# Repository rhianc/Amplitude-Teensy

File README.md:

# PROPRIETARY AMPLITUDE LIGHTING SOFTWARE/HARDWARE REPOSITORY

##  HOW TO CLONE THIS REPO

in unix terminal:

$ git clone --recurse-submodules git@github.com:vfink/amplitude_lights.git

If you do not include the "--recurse-submodules" you will not have the correct library to run the lights

You may need to associate your git account with your computer and should add an SSH key to both your laptop and github account so you don't have to type your password every time. 

## WHERE IS EVERYTHING

24 strip reactive lights:

	master teensy -> amplitude/multi_strip_lights/AmplitudeLights/fftBigBoyMaster
	slave teensy (what you should touch) -> amplitude/multi_strip_lights/AmplitudeLights/fftBigBoyReceiver

8 strip reactive lights:

	amplitude/multi_strip_lights/AmplitudeLights/fftSmallBoy

## TO DO

list ideas and current work here

## NOTES

Cool explanations of why we have to use FreqBinGen and why we SHOULD add some sort of EQ to the processing.
https://www.audiocheck.net/soundtests_nonlinear.php

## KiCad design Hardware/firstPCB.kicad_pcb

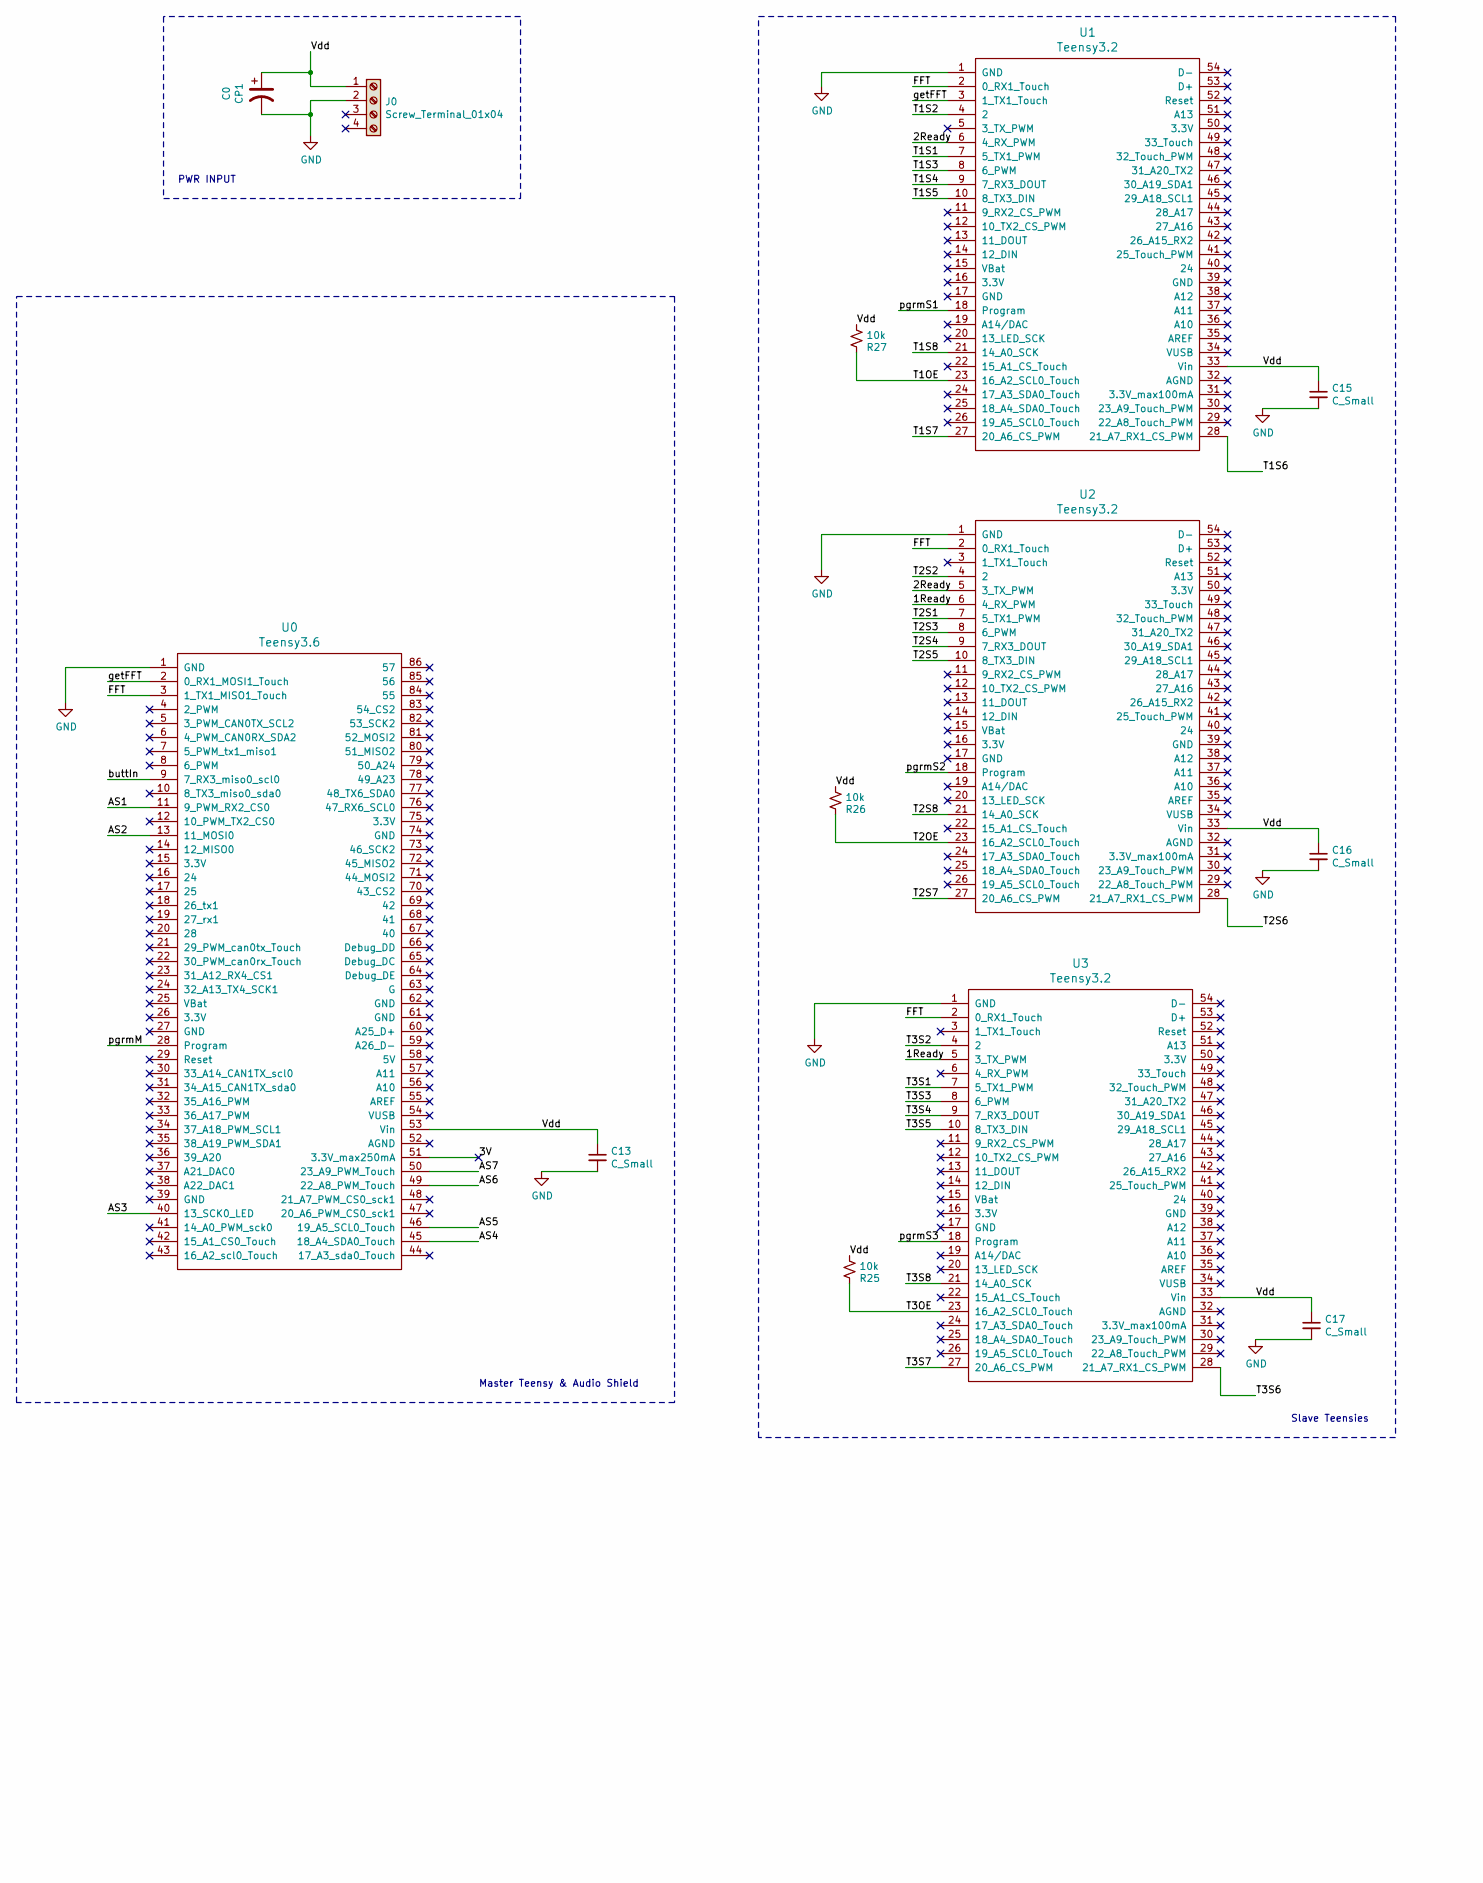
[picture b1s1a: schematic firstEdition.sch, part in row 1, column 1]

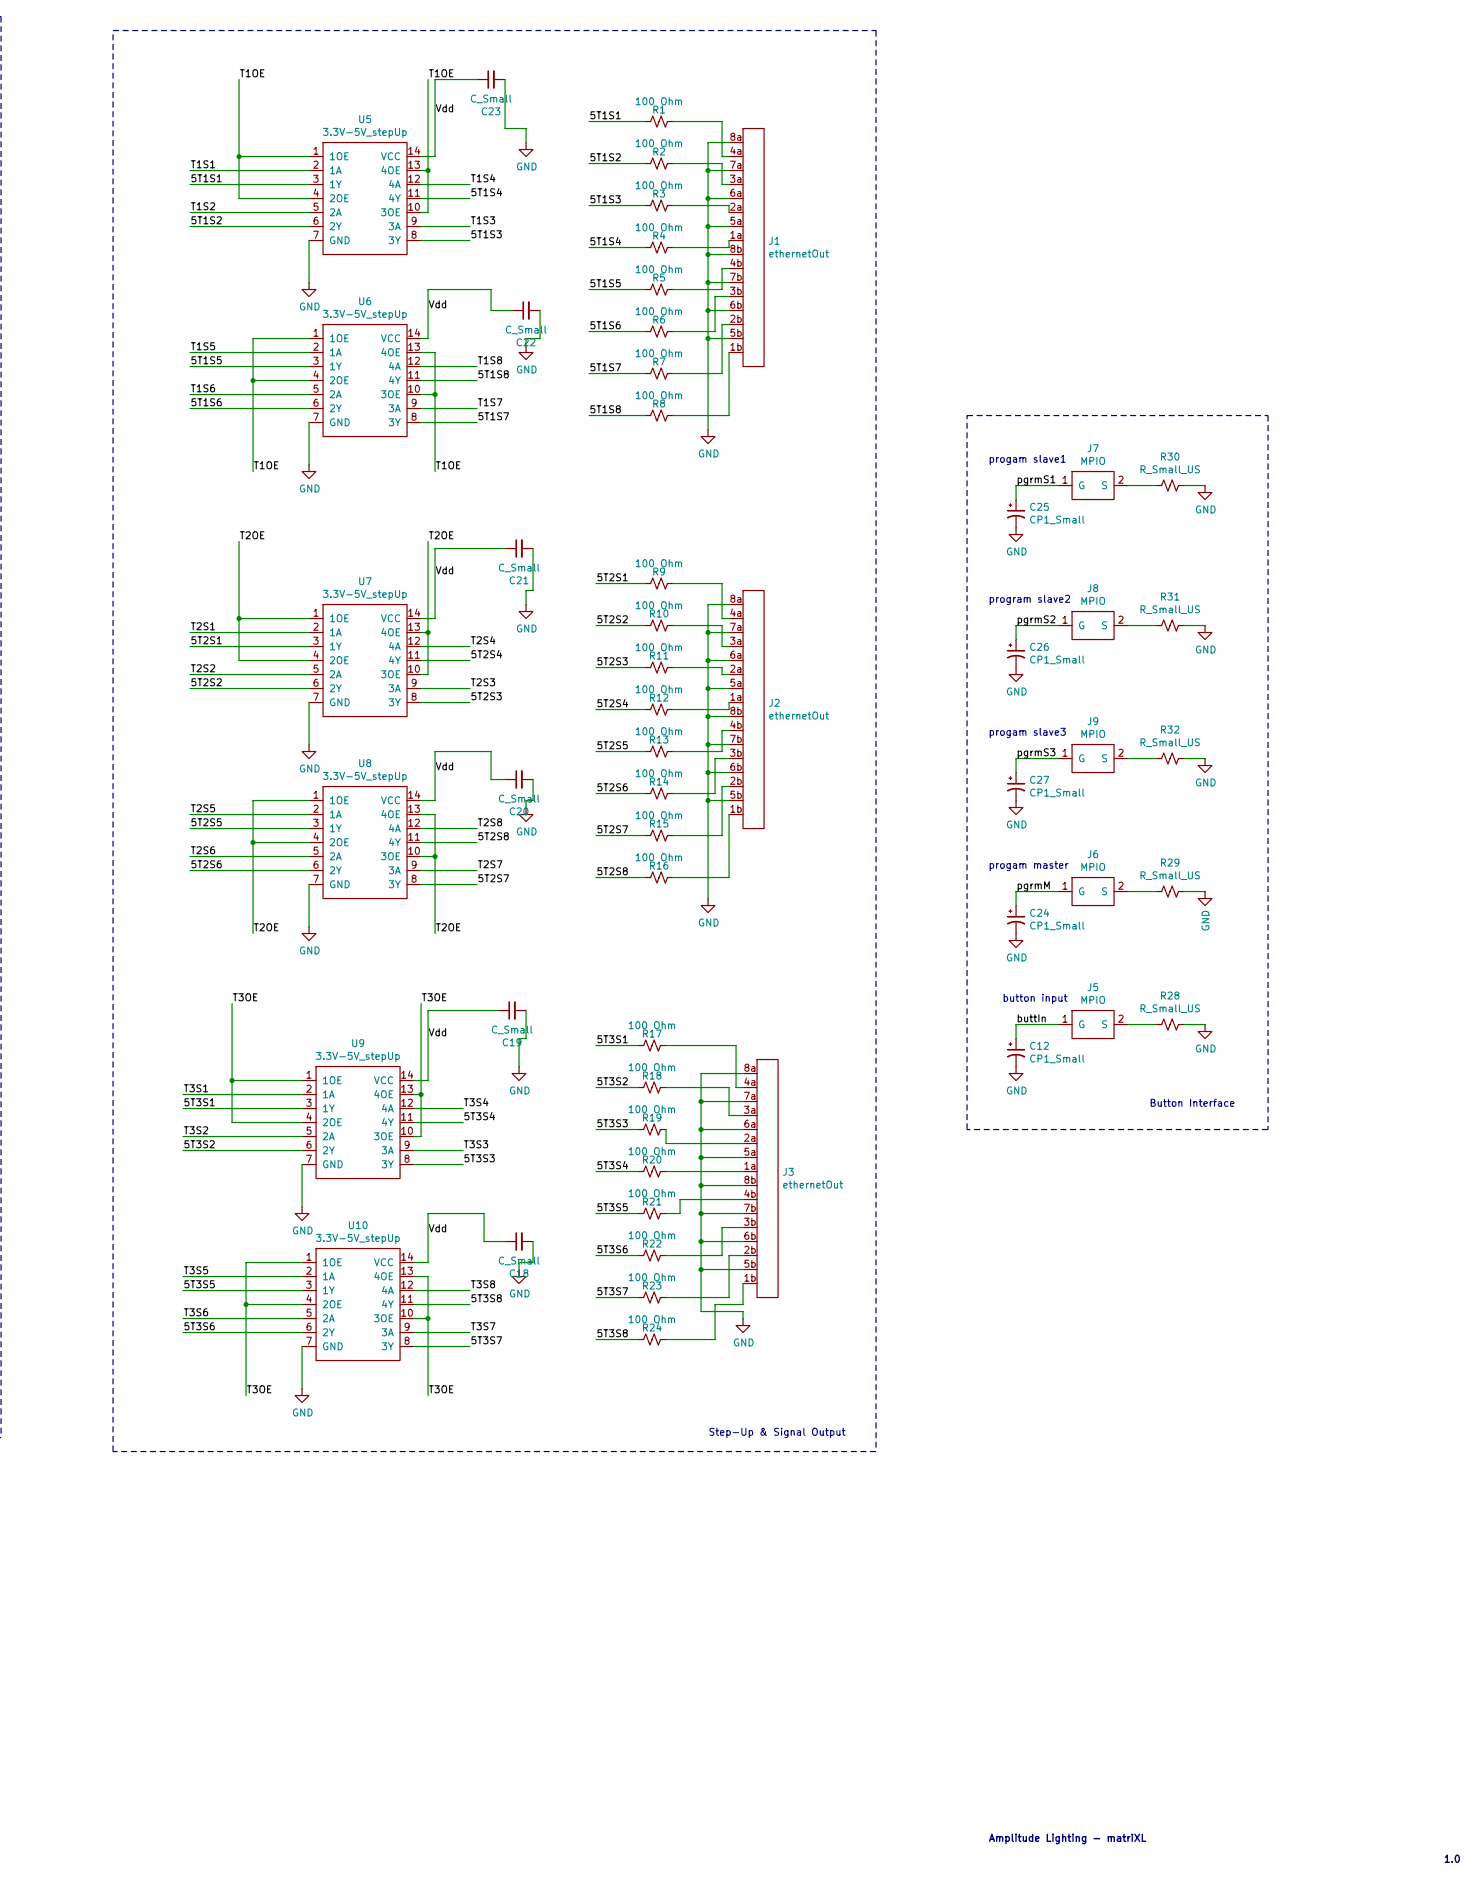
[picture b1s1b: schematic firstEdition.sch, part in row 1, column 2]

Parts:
C0: CP1; CP_Radial_D14.0mm_P7.50mm
C12, C24, C25, C26, C27: CP1_Small; CP_Radial_D6.3mm_P2.50mm
C13, C15, C16, C17, C18, C19, C20, C21, C22, C23: C_Small; CP_Radial_D8.0mm_P3.50mm
J0: Screw_Terminal_01x04; TerminalBlock_bornier-4_P5.08mm
J1, J2, J3: ethernetOut; cat6out
J5, J6, J7, J8, J9: MPIO; 2pinMPIO
R1, R2, R3, R4, R5, R6, R7, R8, R9, R10, R11, R12, R13, R14, R15, R16, R17, R18, R19, R20, R21, R22, R23, R24: 100 Ohm; R_Axial_DIN0309_L9.0mm_D3.2mm_P15.24mm_Horizontal
R25, R26, R27: 10k; R_Axial_DIN0309_L9.0mm_D3.2mm_P15.24mm_Horizontal
R28, R29, R30, R31, R32: R_Small_US; R_Axial_DIN0309_L9.0mm_D3.2mm_P15.24mm_Horizontal
U0: Teensy3.6; Teensy35_36
U1, U2, U3: Teensy3.2; Teensy30_31_32_LC
U5, U6, U7, U8, U9, U10: 3.3V-5V_stepUp; DIP_Socket-14_W4.3_W5.08_W7.62_W10.16_W10.9_3M_214-3339-00-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

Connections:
/1Ready: U2.6 (4_RX_PWM), U3.5 (3_TX_PWM)
/2Ready: U1.6 (4_RX_PWM), U2.5 (3_TX_PWM)
/3V: U0.51 (3.3V_max250mA)
/5T1S1: R1.2, U5.3 (1Y)
/5T1S2: R2.2, U5.6 (2Y)
/5T1S3: R3.2, U5.8 (3Y)
/5T1S4: R4.2, U5.11 (4Y)
/5T1S5: R5.2, U6.3 (1Y)
/5T1S6: R6.2, U6.6 (2Y)
/5T1S7: R7.2, U6.8 (3Y)
/5T1S8: R8.2, U6.11 (4Y)
/5T2S1: R9.2, U7.3 (1Y)
/5T2S2: R10.2, U7.6 (2Y)
/5T2S3: R11.2, U7.8 (3Y)
/5T2S4: R12.2, U7.11 (4Y)
/5T2S5: R13.2, U8.3 (1Y)
/5T2S6: R14.2, U8.6 (2Y)
/5T2S7: R15.2, U8.8 (3Y)
/5T2S8: R16.2, U8.11 (4Y)
/5T3S1: R17.2, U9.3 (1Y)
/5T3S2: R18.2, U9.6 (2Y)
/5T3S3: R19.2, U9.8 (3Y)
/5T3S4: R20.2, U9.11 (4Y)
/5T3S5: R21.2, U10.3 (1Y)
/5T3S6: R22.2, U10.6 (2Y)
/5T3S7: R23.2, U10.8 (3Y)
/5T3S8: R24.2, U10.11 (4Y)
/AS1: U0.11 (9_PWM_RX2_CS0)
/AS2: U0.13 (11_MOSI0)
/AS3: U0.40 (13_SCK0_LED)
/AS4: U0.45 (18_A4_SDA0_Touch)
/AS5: U0.46 (19_A5_SCL0_Touch)
/AS6: U0.49 (22_A8_PWM_Touch)
/AS7: U0.50 (23_A9_PWM_Touch)
/FFT: U0.3 (1_TX1_MISO1_Touch), U1.2 (0_RX1_Touch), U2.2 (0_RX1_Touch), U3.2 (0_RX1_Touch)
/T1OE: R27.2, U1.23 (16_A2_SCL0_Touch), U5.1 (1OE), U5.4 (2OE), U5.10 (3OE), U5.13 (4OE), U6.1 (1OE), U6.4 (2OE), U6.10 (3OE), U6.13 (4OE)
/T1S1: U1.7 (5_TX1_PWM), U5.2 (1A)
/T1S2: U1.4 (2), U5.5 (2A)
/T1S3: U1.8 (6_PWM), U5.9 (3A)
/T1S4: U1.9 (7_RX3_DOUT), U5.12 (4A)
/T1S5: U1.10 (8_TX3_DIN), U6.2 (1A)
/T1S6: U1.28 (21_A7_RX1_CS_PWM), U6.5 (2A)
/T1S7: U1.27 (20_A6_CS_PWM), U6.9 (3A)
/T1S8: U1.21 (14_A0_SCK), U6.12 (4A)
/T2OE: R26.2, U2.23 (16_A2_SCL0_Touch), U7.1 (1OE), U7.4 (2OE), U7.10 (3OE), U7.13 (4OE), U8.1 (1OE), U8.4 (2OE), U8.10 (3OE), U8.13 (4OE)
/T2S1: U2.7 (5_TX1_PWM), U7.2 (1A)
/T2S2: U2.4 (2), U7.5 (2A)
/T2S3: U2.8 (6_PWM), U7.9 (3A)
/T2S4: U2.9 (7_RX3_DOUT), U7.12 (4A)
/T2S5: U2.10 (8_TX3_DIN), U8.2 (1A)
/T2S6: U2.28 (21_A7_RX1_CS_PWM), U8.5 (2A)
/T2S7: U2.27 (20_A6_CS_PWM), U8.9 (3A)
/T2S8: U2.21 (14_A0_SCK), U8.12 (4A)
/T3OE: R25.2, U3.23 (16_A2_SCL0_Touch), U9.1 (1OE), U9.4 (2OE), U9.10 (3OE), U9.13 (4OE), U10.1 (1OE), U10.4 (2OE), U10.10 (3OE), U10.13 (4OE)
/T3S1: U3.7 (5_TX1_PWM), U9.2 (1A)
/T3S2: U3.4 (2), U9.5 (2A)
/T3S3: U3.8 (6_PWM), U9.9 (3A)
/T3S4: U3.9 (7_RX3_DOUT), U9.12 (4A)
/T3S5: U3.10 (8_TX3_DIN), U10.2 (1A)
/T3S6: U3.28 (21_A7_RX1_CS_PWM), U10.5 (2A)
/T3S7: U3.27 (20_A6_CS_PWM), U10.9 (3A)
/T3S8: U3.21 (14_A0_SCK), U10.12 (4A)
/Vdd: C0.1, C13.1, C15.1, C16.1, C17.1, C18.1, C19.1, C20.1, C21.1, C22.1, C23.1, J0.1, R25.1, R26.1, R27.1, U0.53 (Vin), U1.33 (Vin), U2.33 (Vin), U3.33 (Vin), U5.14 (VCC), U6.14 (VCC), U7.14 (VCC), U8.14 (VCC), U9.14 (VCC), U10.14 (VCC)
/buttIn: C12.1, J5.1 (G), U0.9 (7_RX3_miso0_scl0)
/getFFT: U0.2 (0_RX1_MOSI1_Touch), U1.3 (1_TX1_Touch)
/pgrmM: C24.1, J6.1 (G), U0.28 (Program)
/pgrmS1: C25.1, J7.1 (G), U1.18 (Program)
/pgrmS2: C26.1, J8.1 (G), U2.18 (Program)
/pgrmS3: C27.1, J9.1 (G), U3.18 (Program)
GND: C0.2, C12.2, C13.2, C15.2, C16.2, C17.2, C18.2, C19.2, C20.2, C21.2, C22.2, C23.2, C24.2, C25.2, C26.2, C27.2, J0.2, J1.5a, J1.5b, J1.6a, J1.6b, J1.7a, J1.7b, J1.8a, J1.8b, J2.5a, J2.5b, J2.6a, J2.6b, J2.7a, J2.7b, J2.8a, J2.8b, J3.5a, J3.5b, J3.6a, J3.6b, J3.7a, J3.7b, J3.8a, J3.8b, R28.1, R29.1, R30.1, R31.1, R32.1, U0.1 (GND), U1.1 (GND), U2.1 (GND), U3.1 (GND), U5.7 (GND), U6.7 (GND), U7.7 (GND), U8.7 (GND), U9.7 (GND), U10.7 (GND)
unnamed: J1.1a, R4.1
unnamed: J1.1b, R8.1
unnamed: J1.2a, R3.1
unnamed: J1.2b, R7.1
unnamed: J1.3a, R2.1
unnamed: J1.3b, R6.1
unnamed: J1.4a, R1.1
unnamed: J1.4b, R5.1
unnamed: J2.1a, R12.1
unnamed: J2.1b, R16.1
unnamed: J2.2a, R11.1
unnamed: J2.2b, R15.1
unnamed: J2.3a, R10.1
unnamed: J2.3b, R14.1
unnamed: J2.4a, R9.1
unnamed: J2.4b, R13.1
unnamed: J3.1a, R20.1
unnamed: J3.1b, R24.1
unnamed: J3.2a, R19.1
unnamed: J3.2b, R23.1
unnamed: J3.3a, R18.1
unnamed: J3.3b, R22.1
unnamed: J3.4a, R17.1
unnamed: J3.4b, R21.1
unnamed: J5.2 (S), R28.2
unnamed: J6.2 (S), R29.2
unnamed: J7.2 (S), R30.2
unnamed: J8.2 (S), R31.2
unnamed: J9.2 (S), R32.2

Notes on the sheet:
PWR INPUT
button input
progam master
progam slave1
program slave2
progam slave3
Master Teensy & Audio Shield
Slave Teensies
Step-Up & Signal Output
Button Interface
Amplitude Lighting - matriXL
1.0

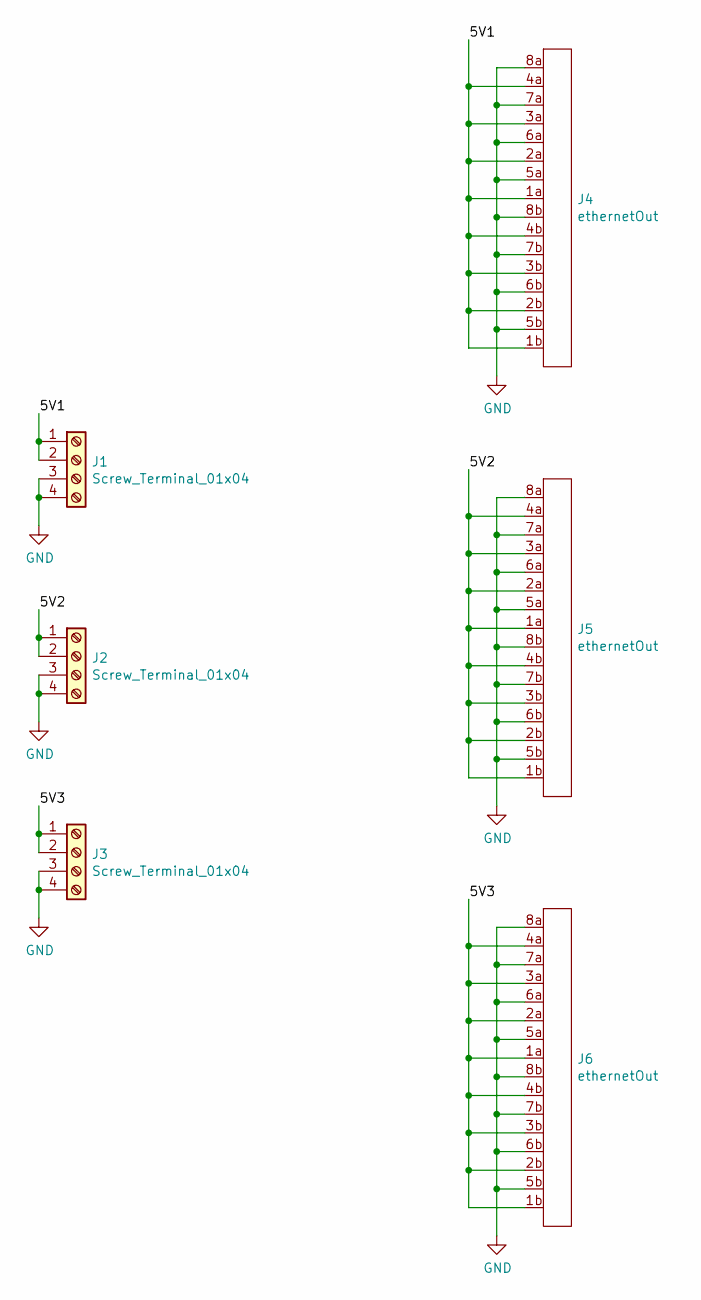
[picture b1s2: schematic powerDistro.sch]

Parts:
J1, J2, J3: Screw_Terminal_01x04
J4, J5, J6: ethernetOut; cat6out

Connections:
unnamed: J1.1, J1.2, J4.1a, J4.1b, J4.2a, J4.2b, J4.3a, J4.3b, J4.4a, J4.4b
unnamed: J1.3, J1.4, J2.3, J2.4, J3.3, J3.4, J4.5a, J4.5b, J4.6a, J4.6b, J4.7a, J4.7b, J4.8a, J4.8b, J5.5a, J5.5b, J5.6a, J5.6b, J5.7a, J5.7b, J5.8a, J5.8b, J6.5a, J6.5b, J6.6a, J6.6b, J6.7a, J6.7b, J6.8a, J6.8b

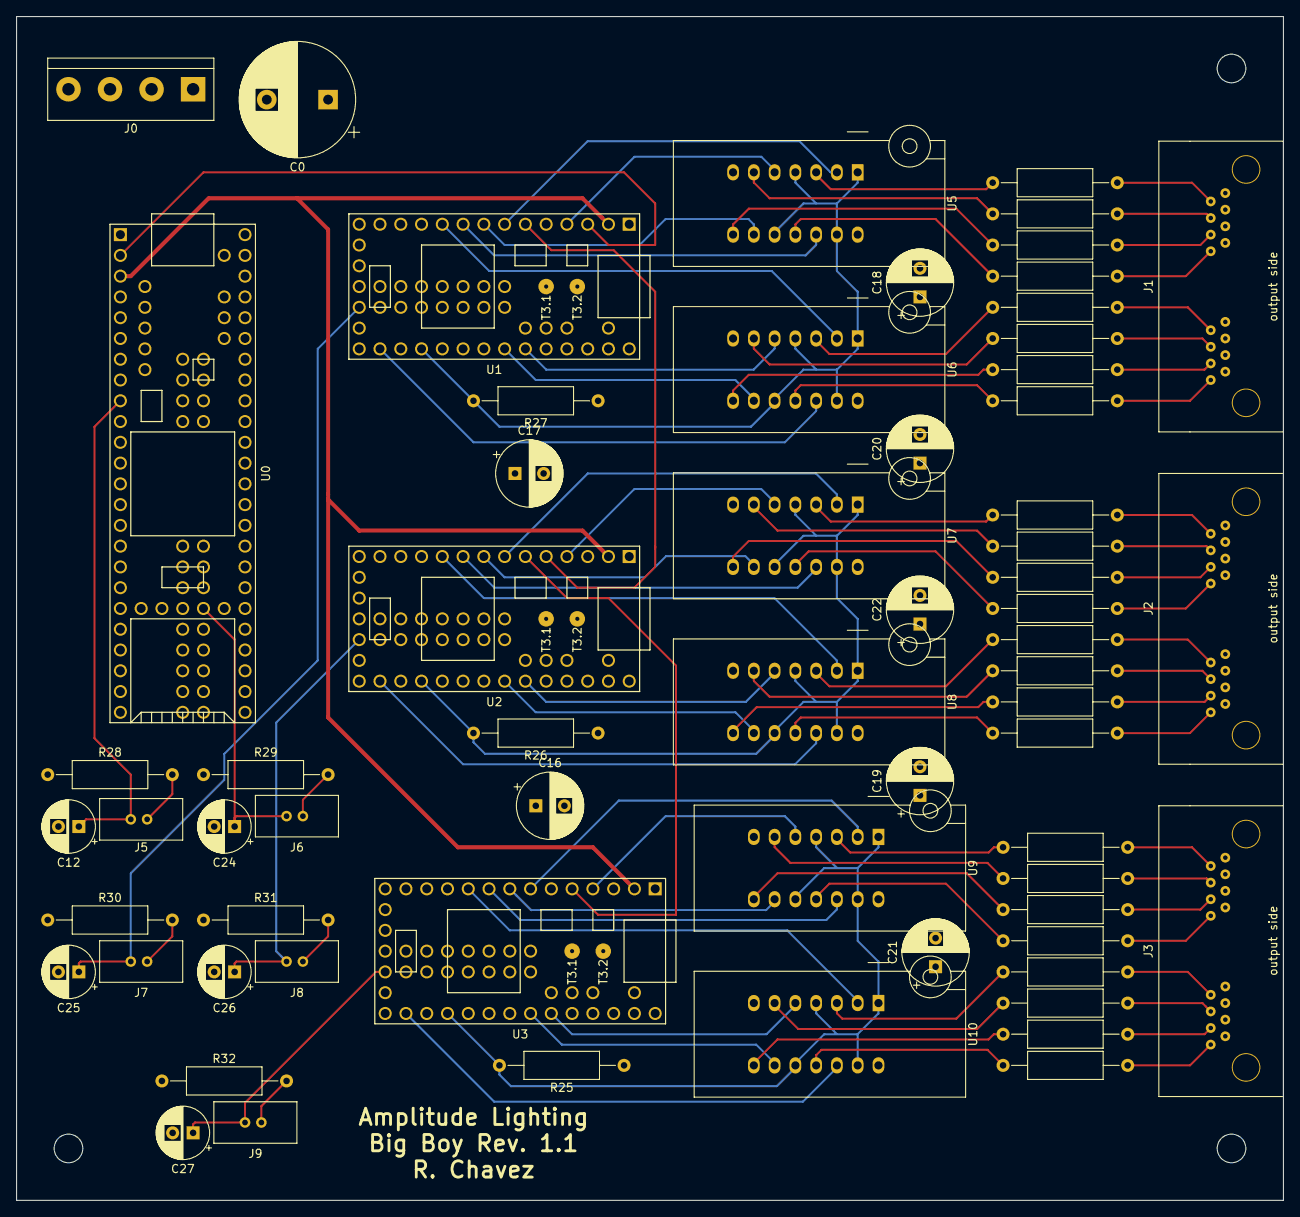
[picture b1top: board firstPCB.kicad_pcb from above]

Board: 4 copper layers, 154.9 x 144.8 mm, 64 parts (0 on the bottom side), 91 nets.

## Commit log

2018-10-20 room light visualizations created with FASTLEDS library
2018-11-14 changed some hsv to rgb
2018-11-14 slightly more dynamic
2018-11-14 switched to FASTLED
2018-11-15 switched to FASTLED plus
2018-11-15 Low frequencies in middle, specturm applied
2018-11-15 changed decay value
2018-11-15 Initial branch commit. Changed frequency bins array to better capture the working range of audio
2018-11-15 Updates frequencyBinsHorizontal spread
2018-11-15 organised code how i like and moved color spec into own func
2018-11-15 no commit
2018-11-15 Revert "changed decay value"
    This reverts commit aa79f20ce36639534fddabe90d7ec2e2242c8d52.
2018-11-15 added some code for color_spectrum, set values to what I want
2018-11-15 actually fixed merge
2018-11-15 made it easier to transition between visualizations. started using generated frequency bins
2018-11-15 base decay on hsv
2018-11-15 minor changes
2018-11-15 fixed formula for frequency bin gen
2018-11-15 fixed frequency bin formula
2018-11-15 partial spectrum added
2018-11-16 alex's code that he couldn't push
2018-11-16 debugged freq bins
2018-11-17 Added ability to move spectrum in time with the sound response bins static, first rough draft needs cleaning
2018-11-17 Added python file to quickly check Frequency bin generator creates values within expected range, and sum to cover the same overall frequency range
2018-11-17 Empty readme file. Things committed last not mentioned - Fixed freqfuncgen algo, cleaned moving_spectrum func, removed deprecated code
2018-11-17 More spectrum tweaks and i still cant use git properly
2018-11-20 Used equal volume curves to make a lazy linear fit approximation function. Will add method to readme, python was used to verify
2018-11-20 More equilizer changes, two part function gives better approximation
2018-11-20 fixed high notes being too sensitive
2018-11-30 flowing like i want
2018-11-30 dont matter
2018-11-30 spectrum wrap
2019-01-10 linear adjustment for level according to bin width
2019-02-23 inital push
2019-02-23 cleaning up everything
2019-02-24 Added button
2019-02-24 added readme
2019-02-24 added off state
2019-02-25 added beat detection
2019-02-25 stash changes
2019-02-25 improved beat detection
2019-02-25 cleaned up a bit
2019-02-25 clean up
2019-04-08 included serial data transfer
2019-04-08 more on data transfer
2019-04-09 initial commit, nothing works
2019-04-09 first real commit. Everything should be working
2019-04-09 serial updates
2019-04-09 working communication
2019-04-09 cleanup
2019-04-09 prepare to add OctoLibrary
2019-04-09 works with 1 strip, now need to make it work with 8
2019-04-09 8 leds per slave working
2019-04-10 added multiSlave
2019-04-10 beat detec spec
2019-04-10 multiTeensy functionality
2019-04-10 added pinOut notes
2019-04-12 3 teensy, need animation edit
2019-04-16 final push
2019-04-18 adjusted serial, made decay a little sharper for better y axis information
2019-04-18 Changed from mono to stereo sound input
2019-04-18 variable name fix in master
2019-08-02 renamed and reformatted folders. removed unnecessary files
2019-08-02 refactored
2019-08-02 added git module for WS2812Serial
2019-08-02 updated readme to help with cloning repo
2019-08-02 added Sean's volume level so I can delete his branch
2019-08-02 moved to consistent snake case naming scheme
2019-08-09 mini time
2019-08-13 added new version of lights code
2019-08-14 added PCB files and working 8 strip
2019-08-14 readme update
2019-08-29 duplicated file to use for my piano notes project. indexed letters for 6x8 pixel maps. working on transferring that to arrays.
2019-08-29 finished lettering
2019-09-03 new lettering branch
2019-09-03 first draft, cant read letters
2019-09-04 completed lettering functionality version 1
2019-09-05 added bluetooth technology
2019-09-05 small change
2019-09-05 fixed bug
2019-09-07 not working
2019-09-07 I think it actually works
2019-09-08 test not working yet
2019-10-26 working with app currently. Want to add static mode and gain control
2019-10-26 should be ready for static
2019-10-29 static can be contolled by app. Everything esle working ok. Sometimes a little buggy
2019-10-29 on/off moved to one button. order testing file now works.
2019-11-02 added gain control
2019-11-16 fixed overflow bug
